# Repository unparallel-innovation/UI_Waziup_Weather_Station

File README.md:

# LoRa Weather Station for Waziup project - by UNPARALLEL Innovation, Lda

This repository provide all information related to the LoRa Weather Station. 
This Weather Station uses LoRa communication technology. It describes the creation of a vigilant weather supervision, composed by multi-tech sensors as part of the IoT sensor node with LoRa network integration. This work was done in the context of Waziup Research Project, which has received funding from the European Union’s H2020 Programme for research, technological development and demonstration under grant agreement No 687607.

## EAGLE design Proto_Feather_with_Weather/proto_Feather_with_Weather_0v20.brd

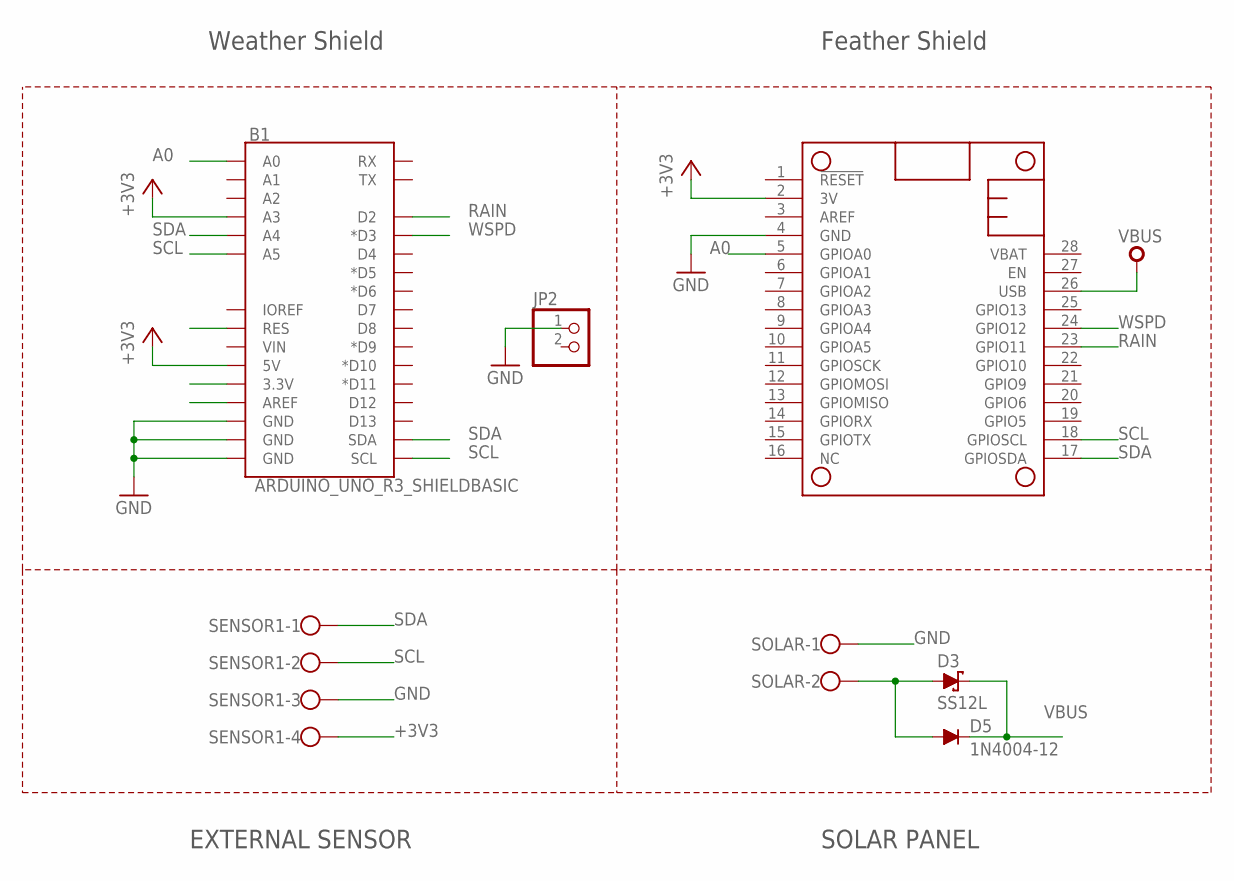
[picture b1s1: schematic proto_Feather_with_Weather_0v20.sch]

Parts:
B1: ARDUINO_UNO_R3_SHIELDBASIC; UNO_R3_SHIELD
D3: SS12L; SUB_SMA_PROTO
D5: 1N4004-12; DO41-12
JP2: PINHD-1X2; 1X02
MS2: FEATHERWING_NODIM; FEATHERWING_DIM
SENSOR1: W237-4
SOLAR: W237-102

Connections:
+3V3: B1.5V, B1.A3, MS2.2 (3V), SENSOR1.4
A0: B1.A0, MS2.5 (GPIOA0)
GND: B1.GND@0 (GND), B1.GND@1 (GND), B1.GND@2 (GND), JP2.1, MS2.4 (GND), SENSOR1.3, SOLAR.1
unnamed: D3.A, D5.A, SOLAR.2
RAIN: B1.D2, MS2.23 (GPIO11)
SCL: B1.A5, B1.SCL, MS2.18 (GPIOSCL), SENSOR1.2
SDA: B1.A4, B1.SDA, MS2.17 (GPIOSDA), SENSOR1.1
VBUS: D3.C, D5.C, MS2.26 (USB)
WSPD: B1.D3 (*D3), MS2.24 (GPIO12)

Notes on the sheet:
Weather Shield
Feather Shield
EXTERNAL SENSOR
SOLAR PANEL

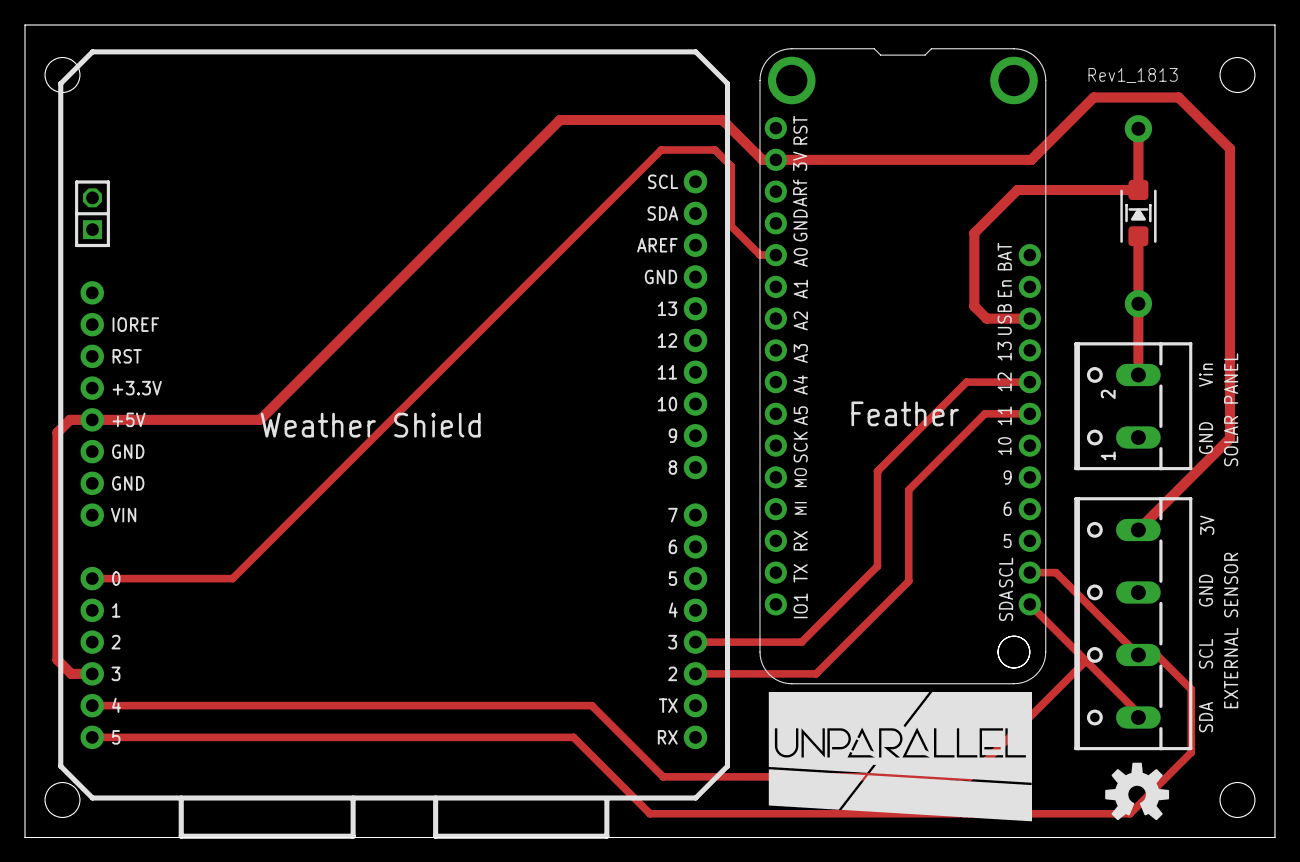
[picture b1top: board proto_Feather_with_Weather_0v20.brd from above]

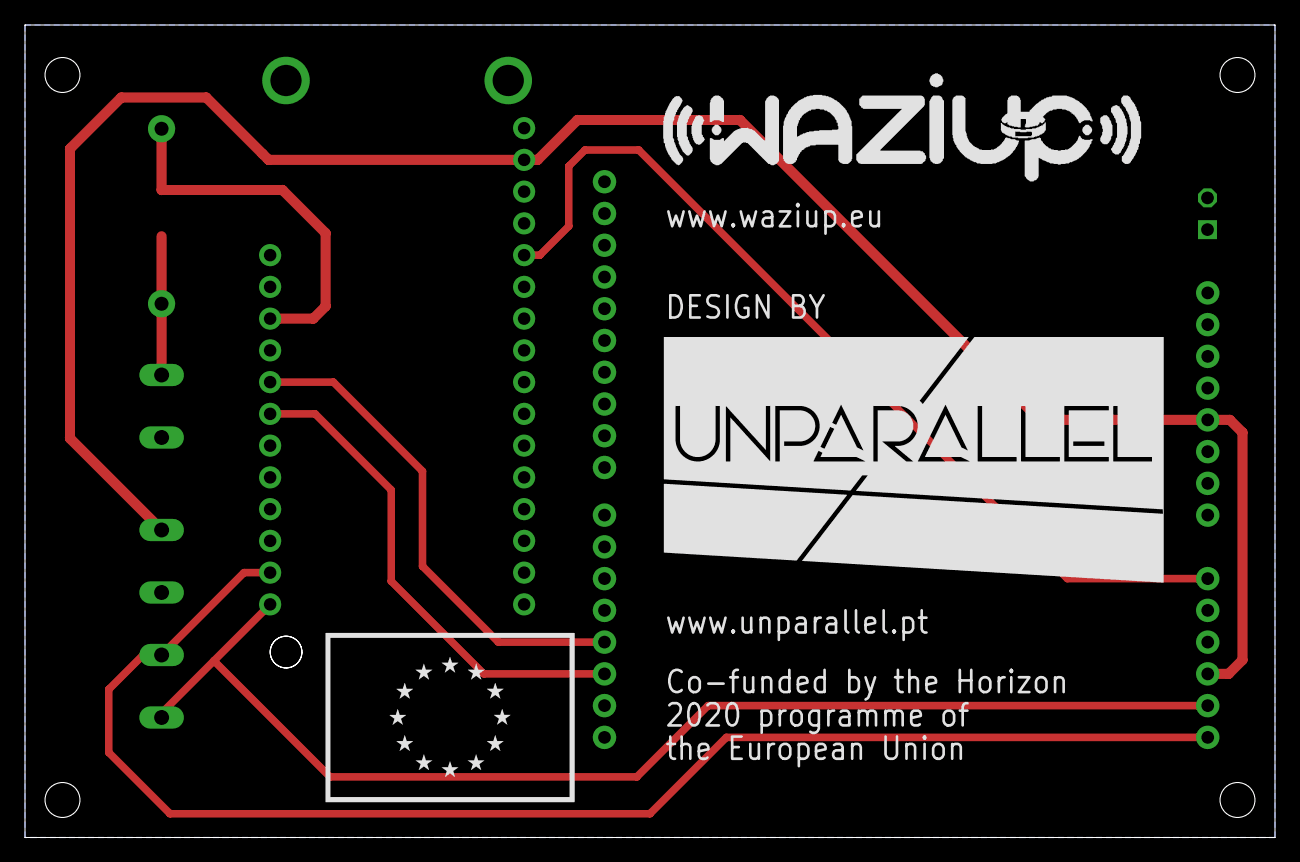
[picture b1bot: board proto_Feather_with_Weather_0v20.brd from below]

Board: 2 copper layers, 100.0 x 65.0 mm, 16 parts (3 on the bottom side), 9 nets.

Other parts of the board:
LOGO1: OSHW-LOGOM; OSHW-LOGO-M
STAND1, STAND2, STAND3, STAND4: MOUNTHOLE_110MIL
U$1: UNPARALLEL_LOGO_NEW_0_INVERT_BIG
U$2: FLAG_EU
U$3: LOGO_WAZIUP_4CM
U$4: UNPARALLEL_LOGO_NEW_0_INVERT_4CM

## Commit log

2016-12-19 ADD client folder
    This weather station folder contains a client version of the weather
    station with the respective library.
2016-12-19 Added lora_gateway folder
2016-12-19 Removed lora_gateway folder
2016-12-19 ADD read file
    ADD read file for weather station client folder
2016-12-19 New readme update
2016-12-20 New read update
2016-12-20 ADD readme update
2016-12-23 Add old folders
2017-01-09 Removed gateway code, added README.md
2017-01-18 Changed folders name
2017-01-18 Create README file
2017-01-18 Updates to README files
2017-01-18 Overall document
2017-02-20 Update!
    Added new necessary libraries and the final v1.0 code!
2017-02-20 Update!
    Added new necessary libraries and the final v1.0 code in the WS folder
2017-02-21 Fixed links on README.md
2017-02-21 .pdf Document
    Little changes in pdf document
2017-02-21 Update
    Change the sleep time and the green led problem.
2017-02-21 Update!
    Document update!
2017-02-21 Update!
    documento update
2017-02-21 Update!
    Document update
2017-02-22 Ready update.
    Changes in the readme file
2017-02-27 Update!!
    Changes in SparkFunMPL3115A2 lib and
    Feather_Lora_WeatherStation_LowPower_RTC code
2017-02-27 Update!
    Folders change.
2017-02-27 Update!!
    Update!!
2017-03-31 Updated freeboard page
2017-03-31 Remove ThingSpeak channel key
2017-04-05 Folder name
    Folder name update
2017-04-06 CloudThingSpeakWeatherStation.py and README.md updated
2017-04-06 Updated thingspeak channel on README.md
2017-04-07 V2.0
    Added version 2 codes and necessary libraries
2017-04-07 Cleaning Simple version
2017-04-07 Update
    ADC table values update
2017-04-07 update
    Readme files updates
2017-04-10 Update
    documents update
2017-08-22 WS v2
2017-08-22 no message
2017-09-04 Solved issues #1 to #3
    Added code to have a better tendency of the wind direction (gets wind
    direction twice per second).
2017-09-28 Update
    Added the LoRaWeatherStation.ino example.
2017-09-28 ThingSpeak API
    Change the ThingSpeak channel id in the “LoRaWeatherStation.ino” example
2017-09-28 Time to run
    Added timeout in the “while(!Serial)”
2017-09-28 library.properties
    Update the version in the “library.properties” file
2017-09-28 Update ThingSpeak Channel doc
    Update the account info.
2017-09-29 Serial.prints update
    Update the Serial.prints messages
2018-04-12 Added PCB Board Schematics for Easy Assembly
2018-11-20 testing

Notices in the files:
parts and their libraries:
SparkFun-Boards: Licensing: Creative Commons ShareAlike 4.0 International - https://creativecommons.org/licenses/by-sa/4.0
SparkFun-Aesthetics: Licensing: CC v3.0 Share-Alike You are welcome to use this library for commercial purposes.
